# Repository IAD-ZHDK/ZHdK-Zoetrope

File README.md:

# ZHdK-Zoetrope

PCB layout for Zoetrope controller using IR sensor. The rotating plate acts as an encoder wheel, allowing for easy change of frame rate.

## Parts

### Motors

- Micro Geared motor `gm12f-n20va` ([play-zone](https://www.play-zone.ch/en/elektromotor-mit-getriebe-gm12f-n20va.html))
- IR sensor `gm12f-n20va` ([Datasheet](https://www.mouser.ch/ds/2/427/tcrt1000-280041.pdf),[Mouser](https://www.mouser.ch/ProductDetail/Vishay-Semiconductors/TCRT1000?qs=%2fha2pyFadujhzXKa660Zaa8%252bPnrPBmGNjsu6nIV46mU%3d))
-  Geared motor large (requires modification of board) `L149-12-43` ([datasheet](https://www.distrelec.ch/Web/Downloads/80/06/05448006.pdf))
-  High Power LED `CXA1304-0000-000C0HC457F` ([datasheet](https://www.mouser.ch/ds/2/90/20130621CLDDS73CXA1304Rev0-267980.pdf),[mouser](https://www.mouser.ch/ProductDetail/941-CXA13040C0HC457F))

## Notes
-  ([Assembly guide](https://github.com/IAD-ZHDK/ZHdK-Zoetrope/blob/master/misc/zootrope3Dguide.pdf))

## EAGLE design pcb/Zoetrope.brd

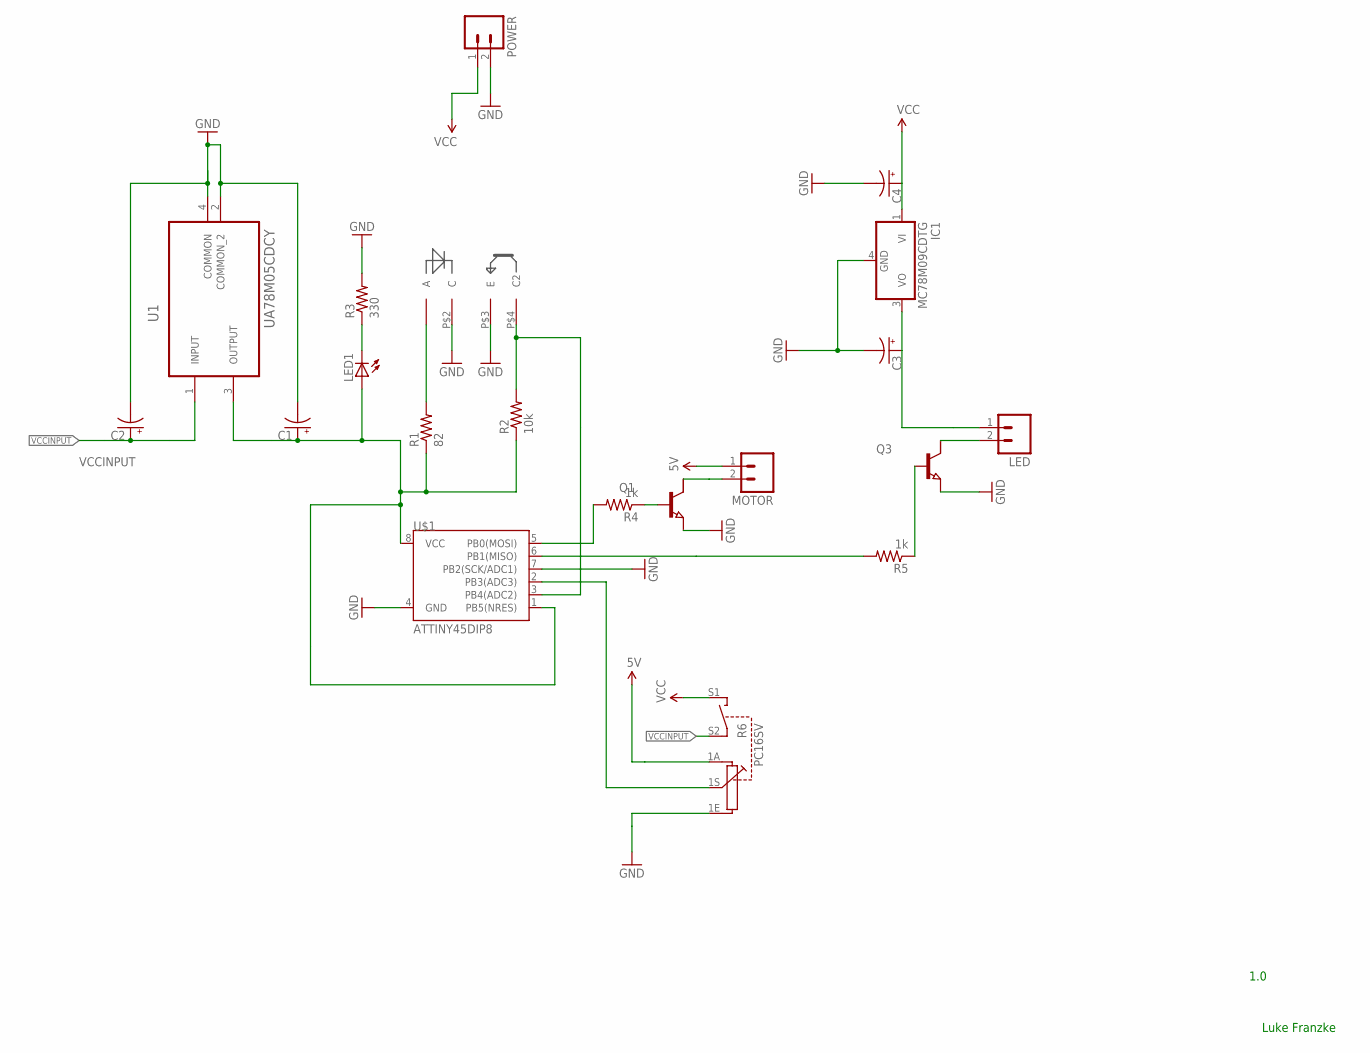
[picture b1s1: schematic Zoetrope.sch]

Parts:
C1, C2, C3, C4: CAP_POL1206; EIA3216
IC1: MC78M09CDTG; DPACK_3
LED: M02; 02P
LED1: LED1206; LED-1206
MOTOR: M02; 02P
POWER: M02; 02P
Q1, Q3: NPN-TRANSISTIOR-2COLSOT89; SOT89
R1: 82; 1206
R2: 10k; 1206
R3: 330; 1206
R4, R5: 1k; 1206
R6: PC16SV
U1: UA78M05CDCY; SOT230P700X180-4N
U$1: ATTINY45DIP8; DIP08
U$2: TCRT1000

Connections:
5V: C1.A (+), LED1.A, MOTOR.1, R1.1, R2.1, R6.1A, U1.3 (OUTPUT), U$1.1 (PB5(NRES)), U$1.8 (VCC)
GND: C1.C (-), C2.C (-), C3.C (-), C4.C (-), IC1.4 (GND), POWER.2, Q1.3 (E), Q3.3 (E), R3.2, R6.1E, U1.2 (COMMON_2), U1.4 (COMMON), U$1.4 (GND), U$1.7 (PB2(SCK/ADC1)), U$2.P$2 (C), U$2.P$3 (E)
unnamed: R5.2, U$1.6 (PB1(MISO))
unnamed: LED1.C, R3.1
unnamed: LED.2, Q3.2 (C)
unnamed: R1.2, U$2.P$1 (A)
unnamed: R2.2, U$1.3 (PB4(ADC2)), U$2.P$4 (C2)
unnamed: R6.1S, U$1.2 (PB3(ADC3))
unnamed: Q3.1 (B), R5.1
unnamed: Q1.1 (B), R4.1
unnamed: R4.2, U$1.5 (PB0(MOSI))
unnamed: MOTOR.2, Q1.2 (C)
unnamed: C3.A (+), IC1.3 (VO), LED.1
VCC: C4.A (+), IC1.1 (VI), POWER.1, R6.S1
VCCINPUT: C2.A (+), R6.S2, U1.1 (INPUT)

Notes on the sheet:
Luke Franzke
1.0

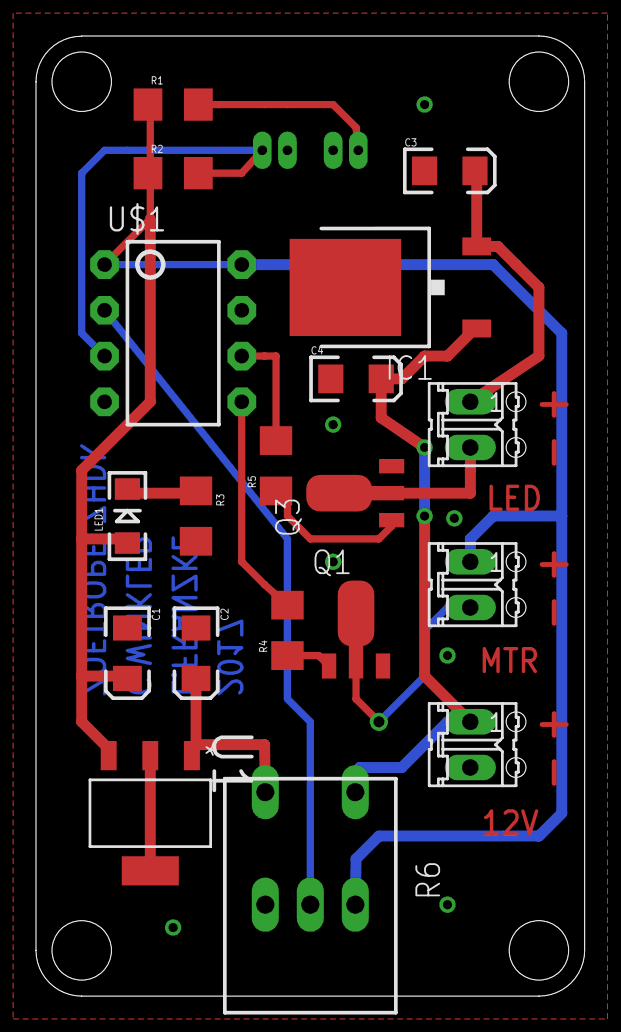
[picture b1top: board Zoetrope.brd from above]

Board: 2 copper layers, 30.5 x 53.3 mm, 24 parts (1 on the bottom side), 15 nets.

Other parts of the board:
U$4, U$5, U$6, U$7: STAND-OFF

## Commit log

2018-03-13 PCB and code added
2018-03-13 added misc material
2018-03-13 Added readme

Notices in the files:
parts and their libraries:
SparkFun-Retired: Licensing:Creative Commons ShareAlike 4.0 International - https://creativecommons.org/licenses/by-sa/4.0
